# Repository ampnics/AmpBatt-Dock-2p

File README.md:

# AmpBatt Dock-2p

An open source 2×18650 power bank designed by the Ampnics community.

| | |
|---|---|
| **Hardware revision** | v0.1.0 (October 2026) |
| **Designer** | Md Ammar Maniyar, Ampnics |
| **Design tool** | KiCad 10 |
| **Status** | Prototype, not yet tested |

## Overview

AmpBatt Dock-2p is a compact power bank board built around the **IP5306** charge-and-boost power management IC. It holds two 18650 lithium-ion cells in a PCB-mounted holder, charges them over USB-C and supplies 5 V to devices through a USB-A port.

## Features

- **Output:** 5 V DC, up to 2.4 A through a USB-A connector
- **Charging input:** USB-C receptacle, power only (5.1 kΩ CC resistors)
- **Battery:** 2 × 18650 cells (BK-18650-PC holder, cells in parallel)
- **Switching frequency:** 500 kHz boost converter with a 1 µH inductor
- **Charge indicator:** 4 LEDs showing about 25 %, 50 %, 75 % and 100 %
- **User control:** push button for wake-up / output on-off (SW1)
- **Expansion:** 2-pin header (J3), This can powerup any 5V

## Repository layout

| Path | Contents |
|---|---|
| `ABD_v01.kicad_pro` | KiCad project file |
| `ABD_v01.kicad_sch` | Schematic |
| `ABD_v01.kicad_pcb` | PCB layout |
| `eeschema/` | Schematic-related files |
| `ext lib/` | External symbol and footprint libraries |
| `ext 3d/` | 3D models |
| `docs/` | Documentation and images |

## Getting started

1. Install [KiCad](https://www.kicad.org/) 10 or newer.
2. Clone this repository:
```bash
   git clone https://github.com/ampnics/AmpBatt-Dock-2p.git
```
3. Open `ABD_v01.kicad_pro` in KiCad.
4. If symbols, footprints or 3D models show as missing, check
   **Preferences → Manage Symbol/Footprint Libraries** and make sure paths use `${KIPRJMOD}`.

## Manufacturing

Gerber and drill files are published under
[Releases](../../releases) for each hardware version.
Suggested PCB settings: Keep it defualt manufacturing setting.

## Safety warning

This design charges and discharges lithium-ion cells. Incorrect assembly, damaged cells, short circuits or poor cell quality can cause fire or injury.
- Use only protected, genuine 18650 cells from a reputable source.
- Never leave charging batteries unattended.
- This is an early prototype and comes with no warranty.
- Build and use it at your own risk.

## Contributing

Issues and pull requests are welcome. Please describe what you changed and why, and which hardware revision it applies to.

© 2026 Ampnics community

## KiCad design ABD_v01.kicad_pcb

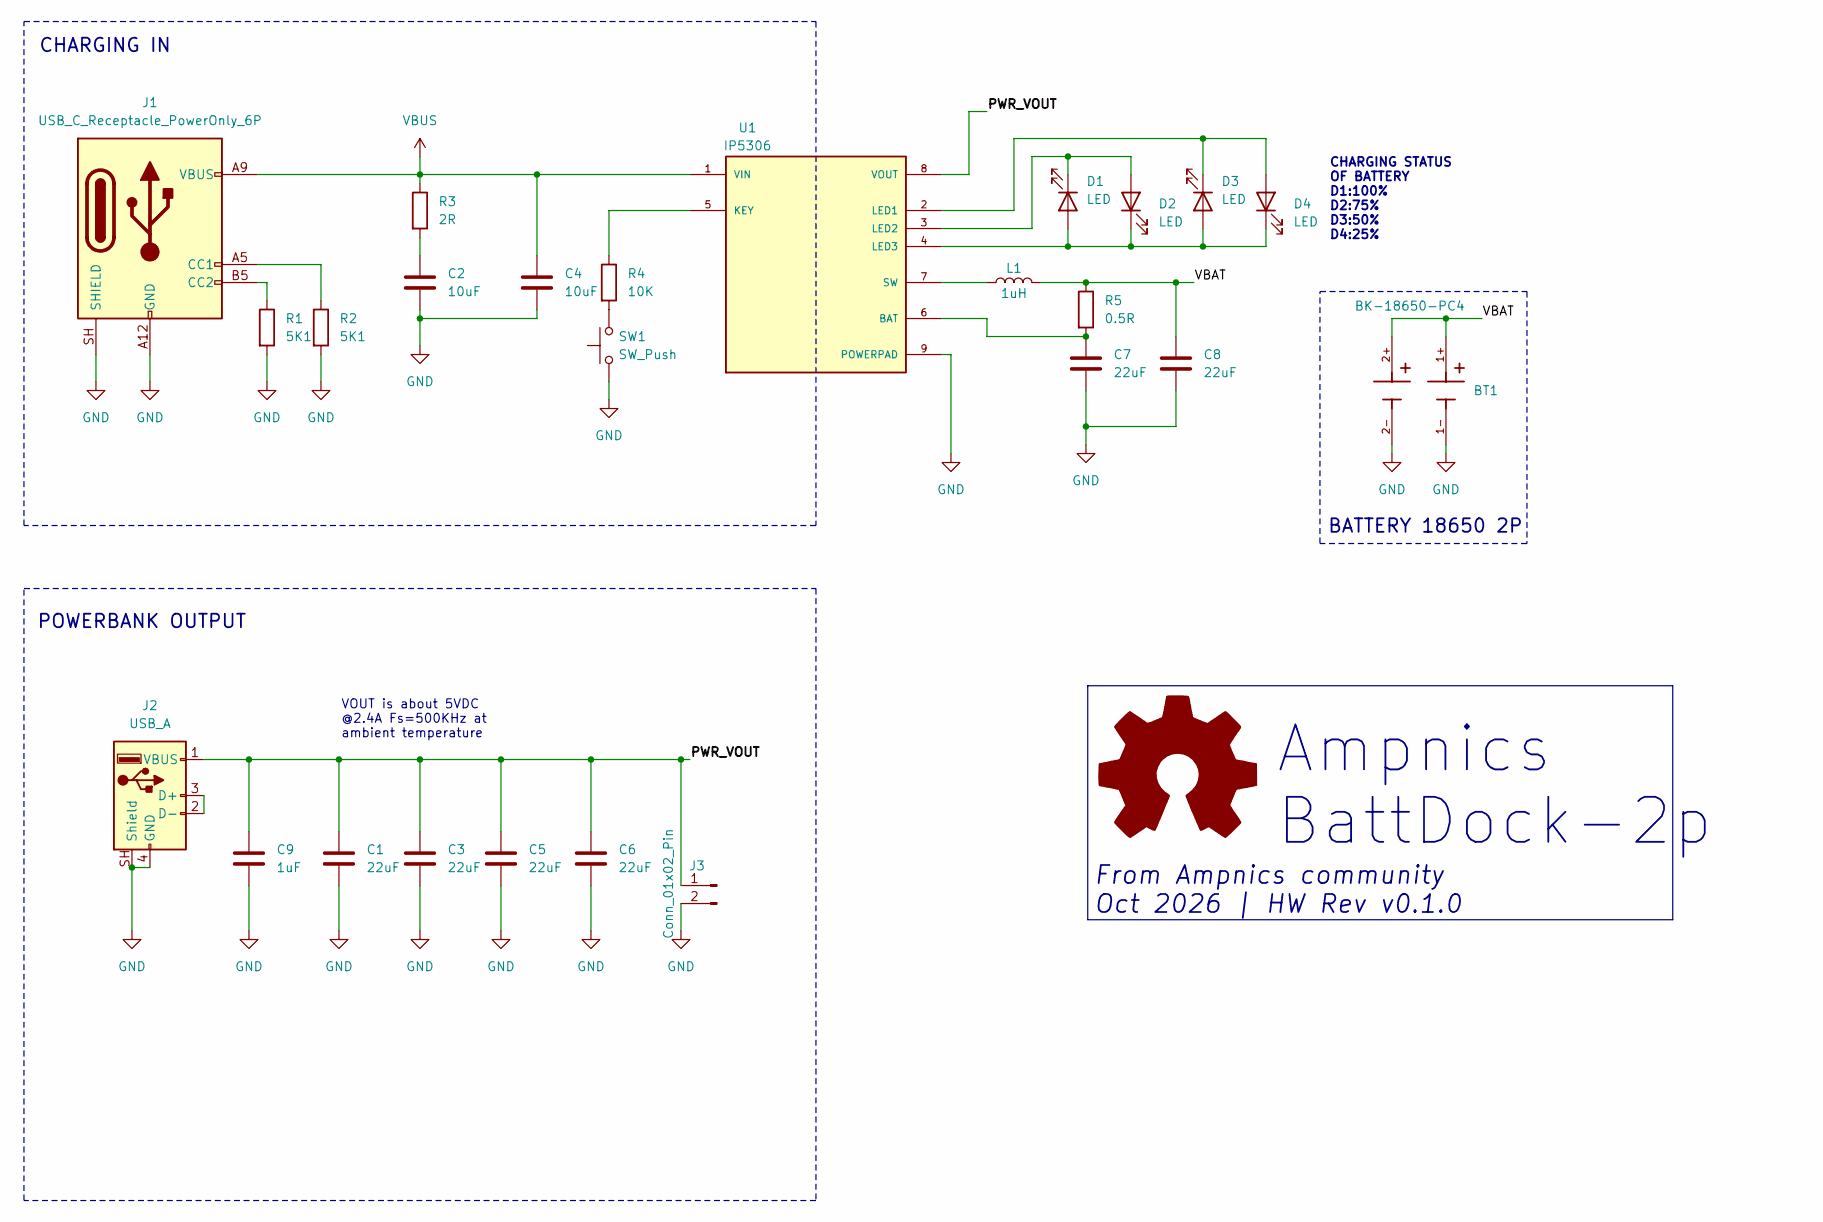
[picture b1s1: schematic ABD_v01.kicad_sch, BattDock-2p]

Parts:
BT1: BK-18650-PC4; BAT_BK-18650-PC4; PARTREV K
C1, C3, C5, C6, C7, C8: 22uF; C_0805_2012Metric
C2, C4: 10uF; C_0805_2012Metric
C9: 1uF; C_0805_2012Metric
D1, D2, D3, D4: LED; LED_0805_2012Metric
J1: USB_C_Receptacle_PowerOnly_6P; USB_C_Receptacle_GCT_USB4125-xx-x-0190_6P_TopMnt_Horizontal
J2: USB_A; USB_A_Stewart_SS-52100-001_Horizontal; MPN 676430910
J3: Conn_01x02_Pin; PinHeader_1x02_P2.54mm_Vertical
L1: 1uH; L_Bourns_SRP7028A_7.3x6.6mm
R1, R2: 5K1; R_0603_1608Metric
R3: 2R; R_0805_2012Metric
R4: 10K; R_0805_2012Metric
R5: 0.5R; R_0805_2012Metric
SW1: SW_Push; SW_Tactile_SPST_Angled_PTS645Vx39-2LFS
U1: IP5306; SOP127P600X165-9N; PARTREV 1.31

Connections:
/PWR_VOUT: C1.1, C3.1, C5.1, C6.1, C9.1, J2.1 (VBUS), J3.1, U1.8 (VOUT)
/VBAT: BT1.1+, BT1.2+, C8.1, L1.2, R5.1
GND: BT1.1-, BT1.2-, C1.2, C2.2, C3.2, C4.2, C5.2, C6.2, C7.2, C8.2, C9.2, J1.A12 (GND), J1.B12 (GND), J1.SH (SHIELD), J2.4 (GND), J2.SH (Shield), J3.2, R1.2, R2.2, SW1.1, U1.9 (POWERPAD)
unnamed: C2.1, R3.2
unnamed: D1.2 (A), D2.1 (K), D3.2 (A), D4.1 (K), U1.4 (LED3)
unnamed: D1.1 (K), D2.2 (A), U1.3 (LED2)
unnamed: D3.1 (K), D4.2 (A), U1.2 (LED1)
unnamed: J1.A5 (CC1), R2.1
unnamed: J1.B5 (CC2), R1.1
unnamed: J2.2 (D-), J2.3 (D+)
unnamed: R4.2, SW1.2
unnamed: C7.1, R5.2, U1.6 (BAT)
unnamed: R4.1, U1.5 (KEY)
unnamed: L1.1, U1.7 (SW)
VBUS: C4.1, J1.A9 (VBUS), J1.B9 (VBUS), R3.1, U1.1 (VIN)

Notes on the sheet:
CHARGING STATUS OF BATTERY D1:100% D2:75% D3:50% D4:25%
Ampnics BattDock-2p
CHARGING IN
POWERBANK OUTPUT
VOUT is about 5VDC @2.4A Fs=500KHz at ambient temperature
BATTERY 18650 2P
From Ampnics community Oct 2026 | HW Rev v0.1.0

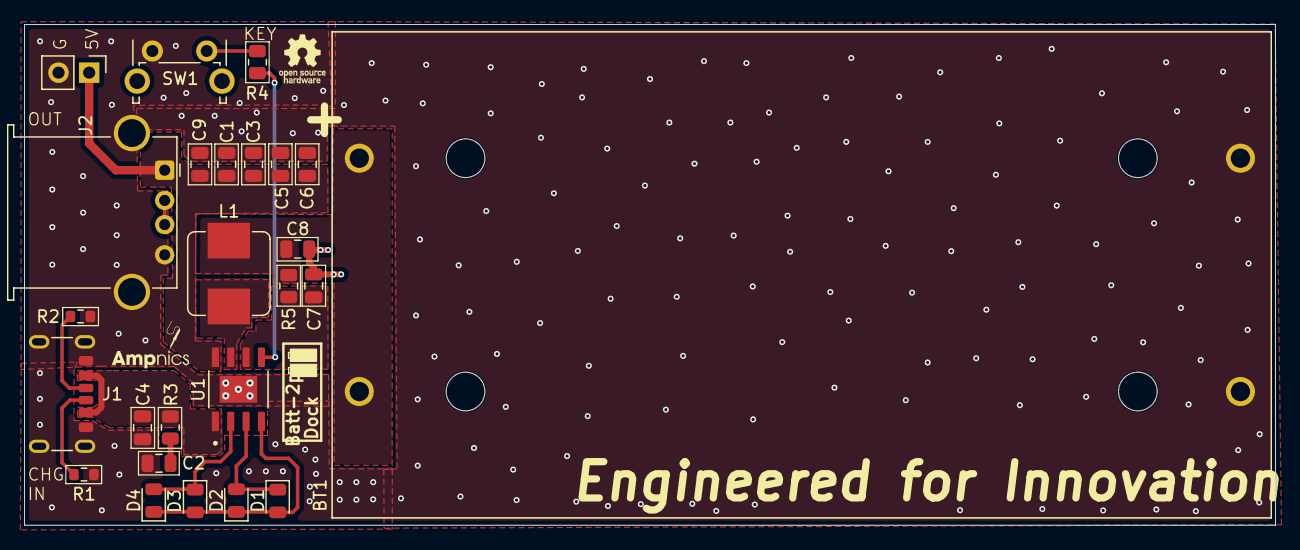
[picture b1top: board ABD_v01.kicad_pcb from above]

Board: 2 copper layers, 103.5 x 41.4 mm, 25 parts (0 on the bottom side), 15 nets.
